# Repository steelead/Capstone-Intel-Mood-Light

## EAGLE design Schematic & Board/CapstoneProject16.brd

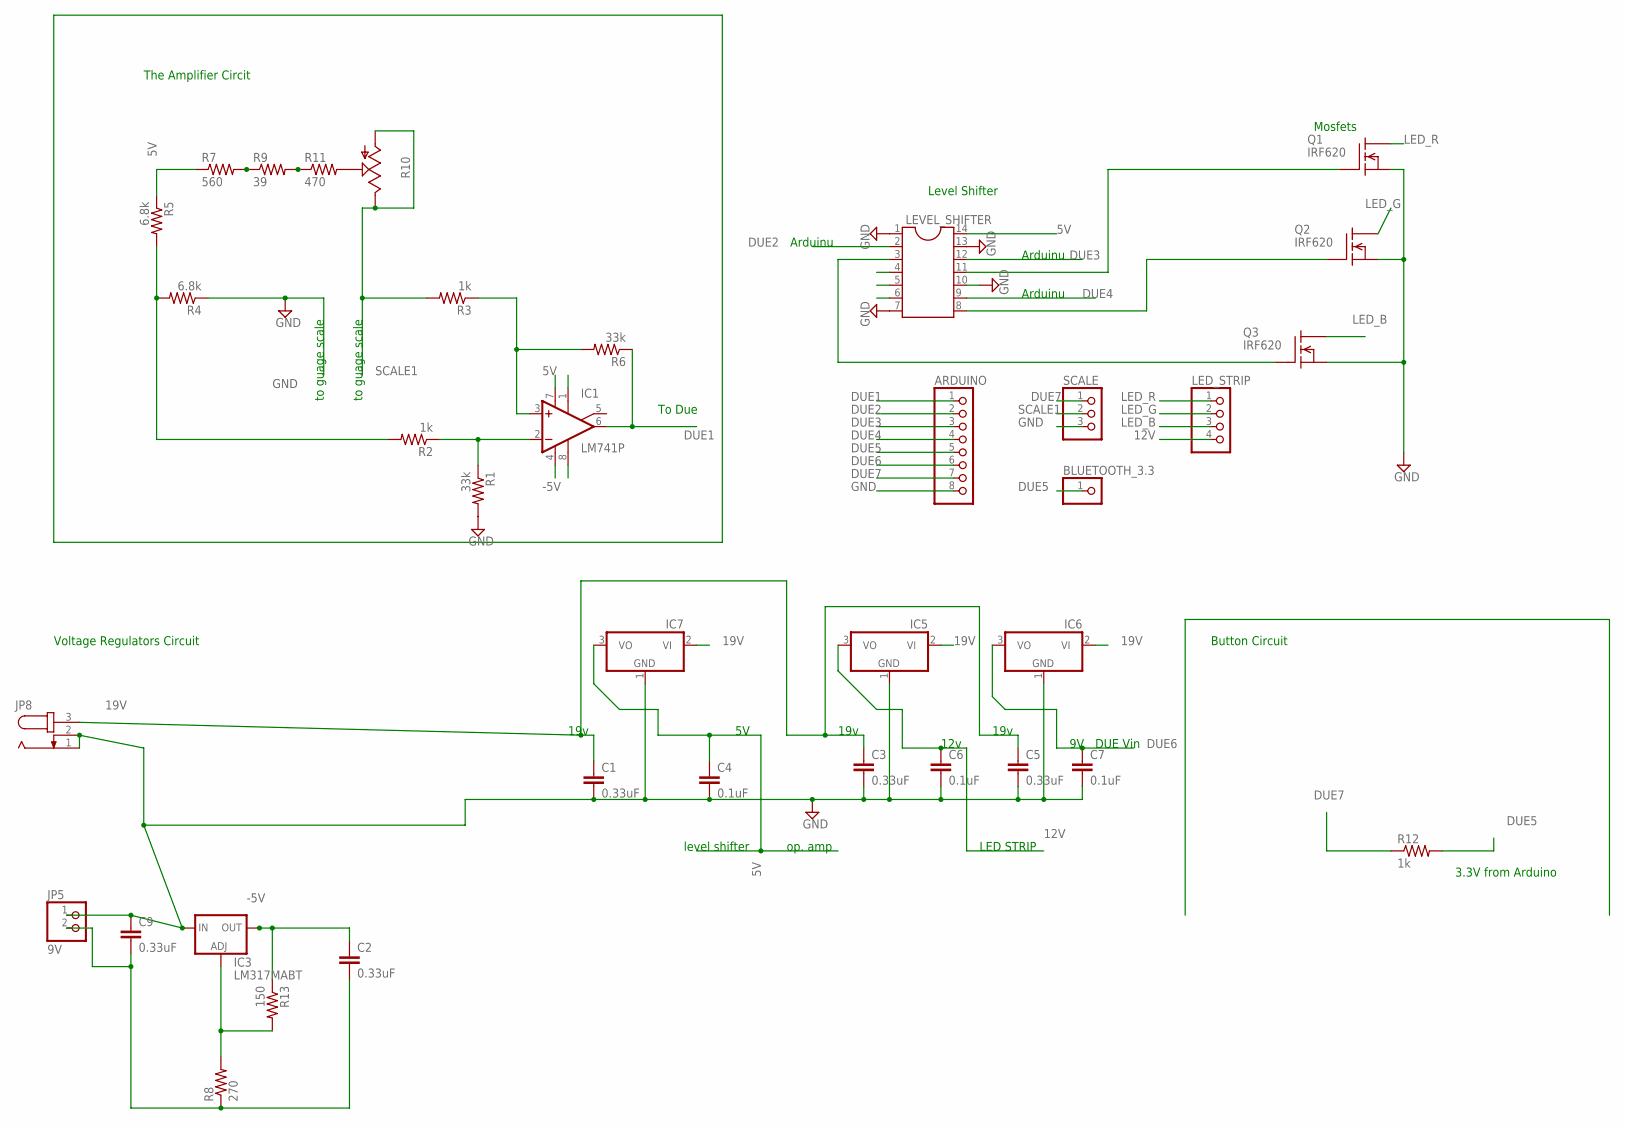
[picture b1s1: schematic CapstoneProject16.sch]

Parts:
ARDUINO: PINHD-1X8; 1X08
BLUETOOTH_3.3: PINHD-1X1; 1X01
C1, C2, C3, C5, C9: 0.33uF; C2.5-3
C4, C6, C7: 0.1uF; C2.5-3
IC1: LM741P; DIL08
IC3: LM317MABT; TO220L1
IC5, IC6: 7905T; TO220H
IC7: 79L05Z; TO92
JP5: 9V; 1X02
JP8: JACK-PLUG1; SPC4078
LED_STRIP: PINHD-1X4; 1X04
LEVEL_SHIFTER: DIL14
Q1, Q2, Q3: IRF620; TO220
R1, R6: 33k; 0204/7
R2, R3, R12: 1k; 0204/7
R4, R5: 6.8k; 0204/7
R7: 560; 0204/7
R8: 270; 0204/7
R9: 39; 0204/7
R10: TRIM_US-S63P; S63P
R11: 470; 0204/7
R13: 150; 0204/7
SCALE: PINHD-1X3; 1X03

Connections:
5V: C4.1, IC1.7 (V+), IC7.3 (VO), LEVEL_SHIFTER.14, R5.1, R7.1
12V: C6.1, IC5.3 (VO), LED_STRIP.4
19V: C1.1, C3.1, C5.1, IC5.2 (VI), IC6.2 (VI), IC7.2 (VI), JP8.3
-5V: C2.1, IC1.4 (V-), IC3.2 (OUT), R13.1
DUE1: ARDUINO.1, IC1.6 (OUT), R6.1
DUE2: ARDUINO.2, LEVEL_SHIFTER.2
DUE3: ARDUINO.3, LEVEL_SHIFTER.12
DUE4: ARDUINO.4, LEVEL_SHIFTER.9
DUE5: ARDUINO.5, BLUETOOTH_3.3.1, R12.2
DUE6: ARDUINO.6, C7.1, IC6.3 (VO)
DUE7: ARDUINO.7, R12.1, SCALE.1
GND: ARDUINO.8, C1.2, C3.2, C4.2, C5.2, C6.2, C7.2, C9.1, IC3.3 (IN), IC5.1 (GND), IC6.1 (GND), IC7.1 (GND), JP5.1, JP8.1, JP8.2, LEVEL_SHIFTER.1, LEVEL_SHIFTER.7, LEVEL_SHIFTER.10, LEVEL_SHIFTER.13, Q1.3 (S), Q2.3 (S), Q3.3 (S), R1.2, R4.1, SCALE.3
LED_B: LED_STRIP.3, Q3.2 (D)
LED_G: LED_STRIP.2, Q2.2 (D)
LED_R: LED_STRIP.1, Q1.2 (D)
unnamed: R2.2, R4.2, R5.2
unnamed: IC1.2 (-IN), R1.1, R2.1
unnamed: IC1.3 (+IN), R3.1, R6.2
unnamed: R10.S, R11.2
unnamed: R7.2, R9.1
unnamed: C2.2, C9.2, JP5.2, R8.1
unnamed: IC3.1 (ADJ), R8.2, R13.2
unnamed: R9.2, R11.1
unnamed: LEVEL_SHIFTER.11, Q1.1 (G)
unnamed: LEVEL_SHIFTER.8, Q2.1 (G)
unnamed: LEVEL_SHIFTER.3, Q3.1 (G)
SCALE1: R3.2, R10.A, R10.E, SCALE.2

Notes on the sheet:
The Amplifier Circit
Voltage Regulators Circuit
To Due
to guage scale
Arduinu
Button Circuit
19v
op. amp
level shifter
DUE Vin
12v
LED STRIP
Level Shifter
Mosfets
3.3V from Arduino

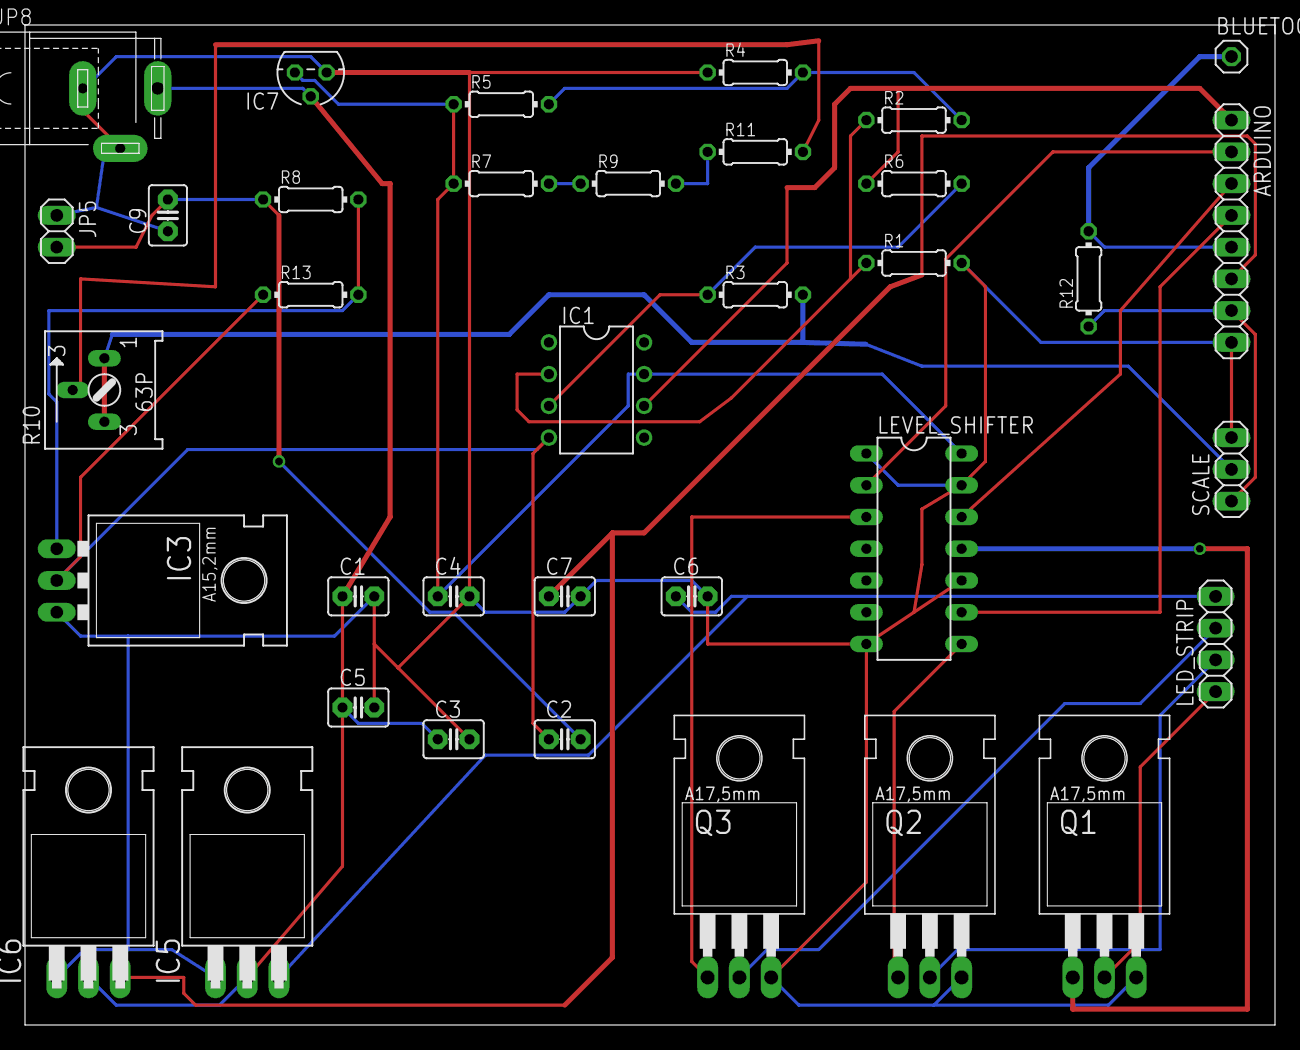
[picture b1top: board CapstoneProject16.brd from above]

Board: 2 copper layers, 100.0 x 80.0 mm, 36 parts (0 on the bottom side), 27 nets.

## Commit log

2016-01-19 Update LICENSE.md
    license file
2016-01-20 test adding file
    this is a test file
2016-01-20 remove test file
2016-01-20 TESTING THE FILE
2016-01-20 adrian add test
2016-01-20 TESTING THE GITHUB
2016-01-20 my test
2016-01-20 bander
2016-01-20 testing editing files
2016-01-20 removing test file
2016-01-20 Added project plans
2016-01-20 moved to folder
2016-01-24 Added Project Proposal
2016-02-03 added test load cell arduino sketch
2016-02-28 hope im doing this right
2016-03-06 t latest commit
2016-03-06 uses button
2016-04-12 code for merging LED Strip code and Weight sensor
2016-05-16 commit includes new board and schematic plus some updated code
2016-05-19 Small test arduino functions to test different components of the new features being added to the main (complete) program
2016-05-20 final code for arduino and pc program for connecting to arduino, not quite finished yet
2016-05-24 Added new test files to test different components that will be integrated into the final code.
    testNewWeight.ino is the new method of getting the weight where when someone steps on the scale we take several samples and compare them, making sure that the values are constant (within some error r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
    The second script testStringSearch.ino is just some code to be able to check a character array string and search for a character within it, and return the index.
2016-05-24 added test code to convert a string to an array of characters
2016-05-24 board and schematic final version
2016-05-30 updated final code for user interface and arduino. Allows 3 main methods of user interface: add, remove, and modifing of user profiles (grouping of name, color, and weight).
2016-05-31 updated final code, fixed run errors, first tested version
2016-06-04 Project Report
    Details of the project
